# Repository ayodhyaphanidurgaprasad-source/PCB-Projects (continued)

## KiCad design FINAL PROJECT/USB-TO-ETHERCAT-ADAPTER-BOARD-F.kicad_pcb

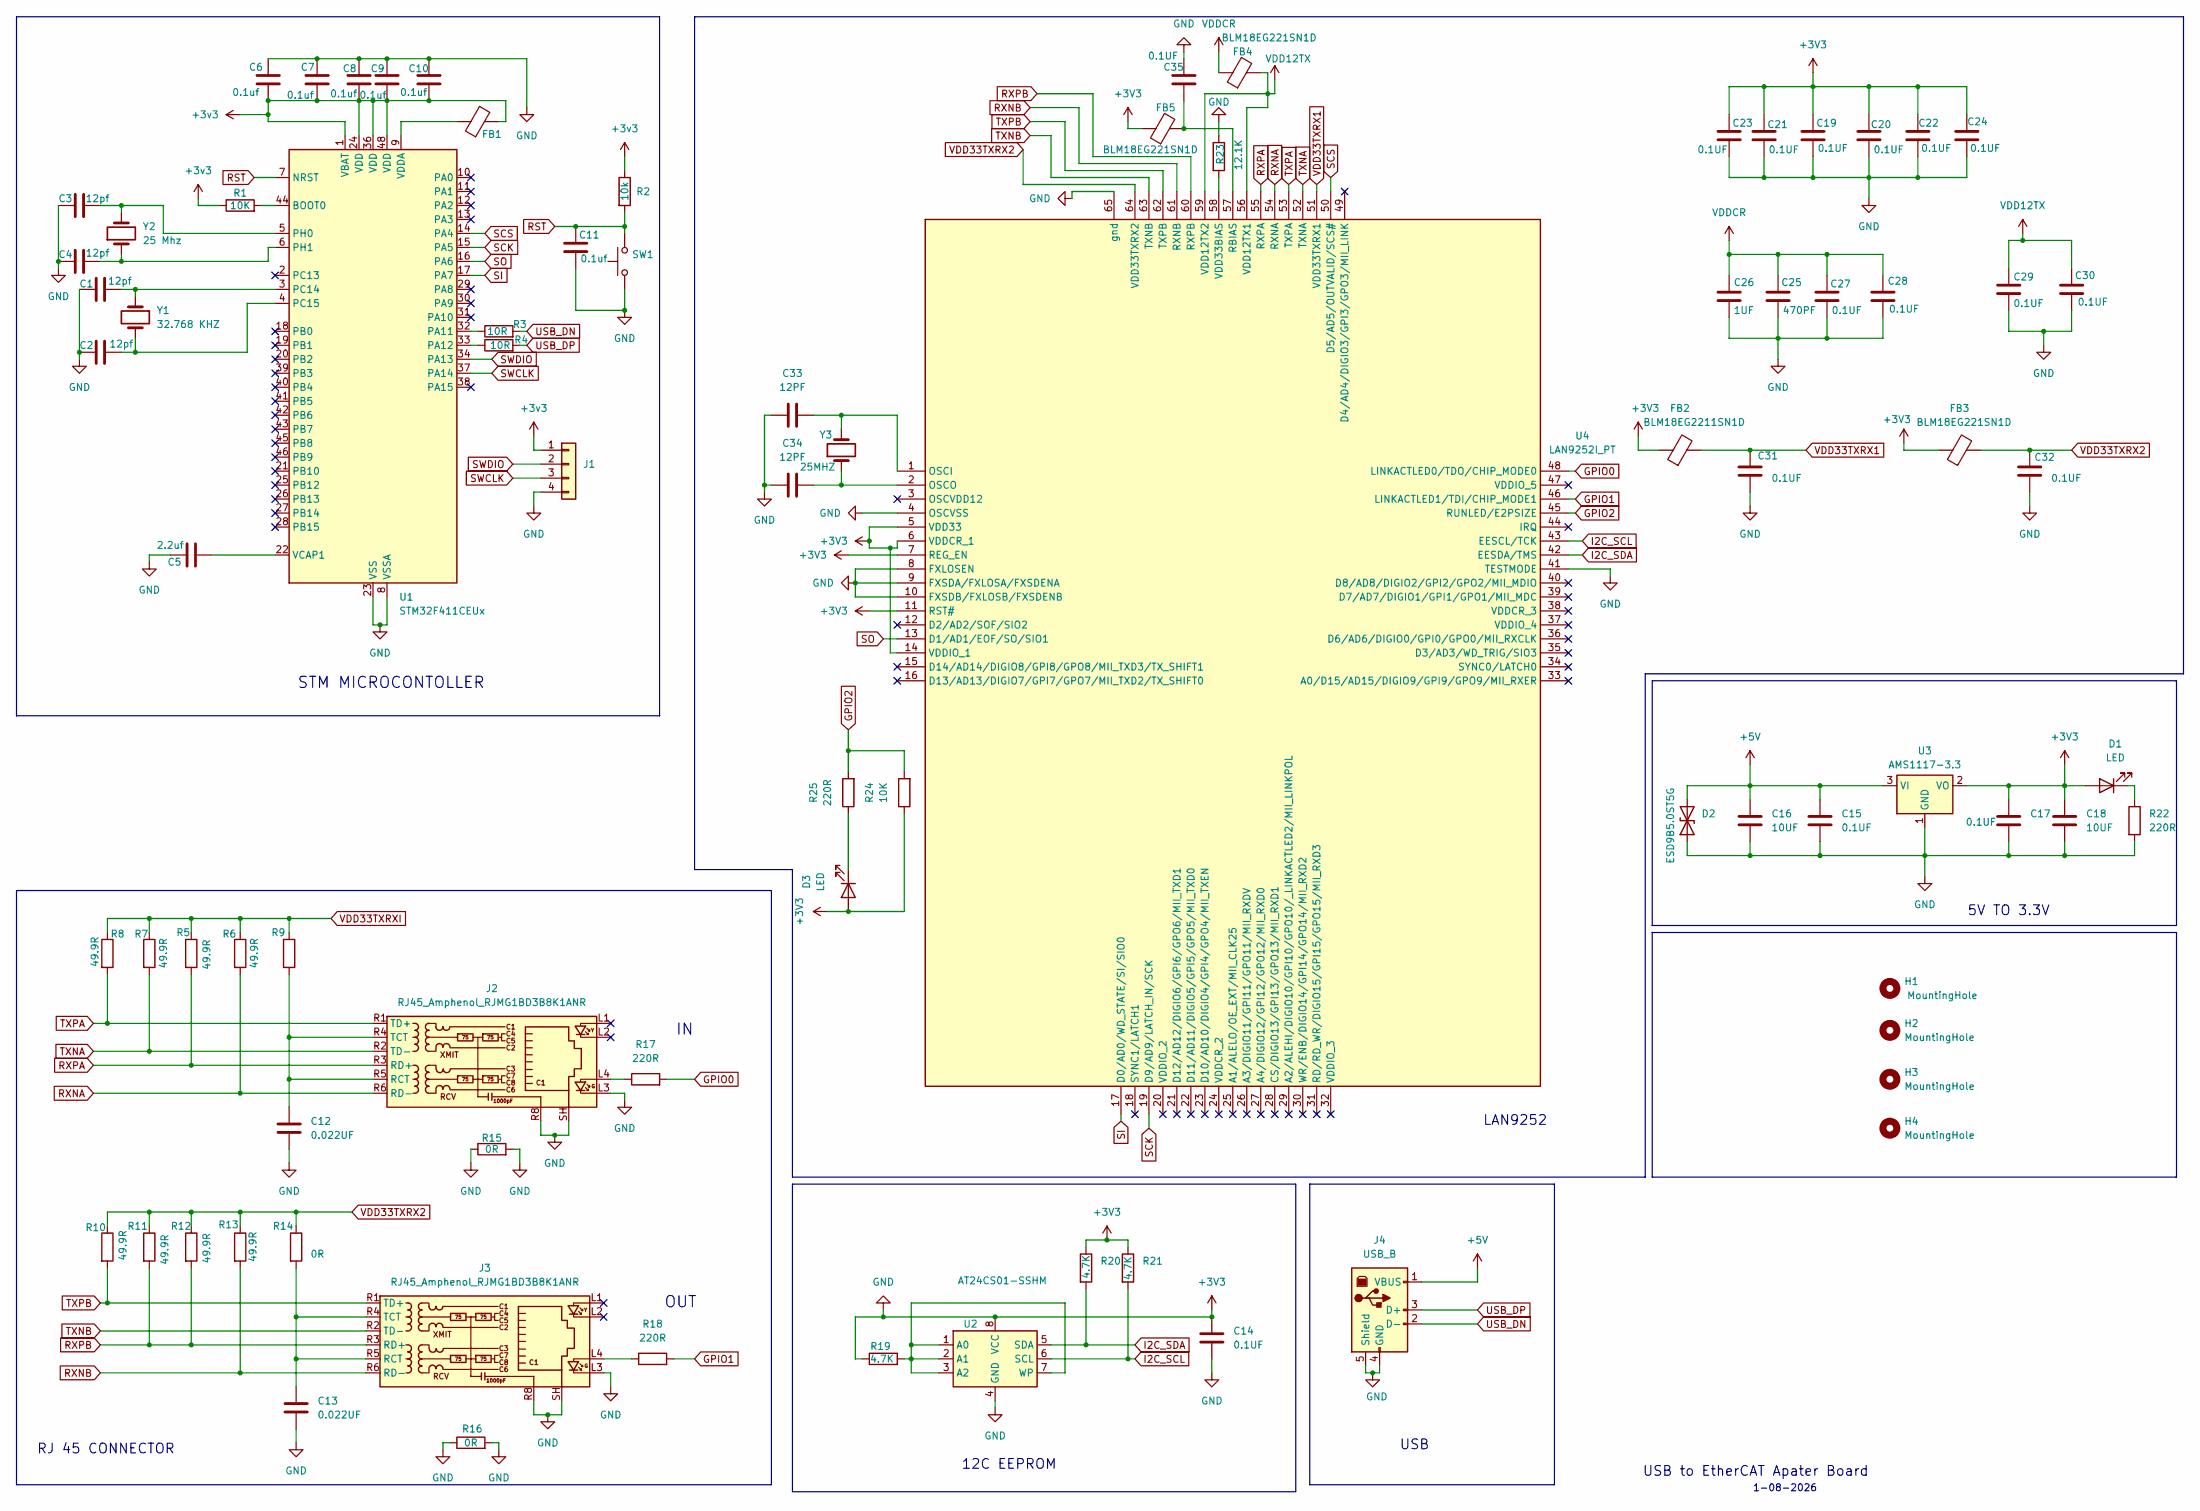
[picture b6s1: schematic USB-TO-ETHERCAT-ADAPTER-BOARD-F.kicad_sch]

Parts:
C1, C2, C3, C4: 12pf; C_0805_2012Metric
C5: 2.2uf; C_0805_2012Metric
C6, C7, C8, C9, C10, C11: 0.1uf; C_0805_2012Metric
C12, C13: 0.022UF; C_0805_2012Metric
C14, C15, C17, C19, C20, C21, C22, C23, C24, C27, C28, C29, C30, C31, C32, C35: 0.1UF; C_0805_2012Metric
C16, C18: 10UF; C_0805_2012Metric
C25: 470PF; C_0805_2012Metric
C26: 1UF; C_0805_2012Metric
C33, C34: 12PF; C_0805_2012Metric
D1, D3: LED; LED_0805_2012Metric
D2: ESD9B5.0ST5G; D_0805_2012Metric
FB1: FerriteBead; L_0603_1608Metric
FB2: BLM18EG2211SN1D; L_0603_1608Metric
FB3, FB4, FB5: BLM18EG221SN1D; L_0603_1608Metric
H1, H2, H3, H4: MountingHole; MountingHole_2.2mm_M2
J1: Conn_01x04; PinHeader_1x04_P1.27mm_Vertical
J2, J3: RJ45_Amphenol_RJMG1BD3B8K1ANR
J4: USB_B; USB_A_Molex_67643_Horizontal
R1, R24: 10K; R_0805_2012Metric
R2: 10k; R_0805_2012Metric
R3, R4: 10R; R_0805_2012Metric
R5, R6, R7, R8, R10, R11, R12, R13: 49.9R; R_0805_2012Metric
R9: R_0805_2012Metric
R14, R15, R16: 0R; R_0805_2012Metric
R17, R18, R22, R25: 220R; R_0805_2012Metric
R19, R20, R21: 4.7K; R_0805_2012Metric
R23: 12.1K; R_0805_2012Metric
SW1: SW_Push; SW_Push_SPST_NO_Alps_SKRK
U1: STM32F411CEUx; QFN-48-1EP_7x7mm_P0.5mm_EP5.15x5.15mm
U2: AT24CS01-SSHM; SOIC-8_3.9x4.9mm_P1.27mm
U3: AMS1117-3.3; SOT-223-3_TabPin2
U4: LAN9252I_PT; QFP50P1200X1200X120-65N; Manufacturer_Part_Number LAN9252I/PT; Mouser Part Number 579-LAN9252I/PT
Y1: 32.768 KHZ; Crystal_SMD_3215-2Pin_3.2x1.5mm
Y2: 25 Mhz; Crystal_SMD_HC49-SD
Y3: 25MHZ; Crystal_SMD_HC49-SD

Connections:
+5V: C15.1, C16.1, D2.2 (A2), J4.1 (VBUS), U3.3 (VI)
GPIO0: R17.2, U4.48 (LINKACTLED0/TDO/CHIP_MODE0)
GPIO1: R18.2, U4.46 (LINKACTLED1/TDI/CHIP_MODE1)
GPIO2: R24.2, R25.2, U4.45 (RUNLED/E2PSIZE)
I2C_SCL: R21.2, U2.6 (SCL), U4.43 (EESCL/TCK)
I2C_SDA: R20.2, U2.5 (SDA), U4.42 (EESDA/TMS)
unnamed: D1.1 (K), R22.1
unnamed: D3.1 (K), R25.1
unnamed: J2.L4, R17.1
unnamed: C12.1, J2.R4 (TCT), J2.R5 (RCT), R9.2
unnamed: J3.L4, R18.1
unnamed: C13.1, J3.R4 (TCT), J3.R5 (RCT), R14.2
unnamed: R1.2, U1.44 (BOOT0)
unnamed: R3.1, U1.32 (PA11)
unnamed: R4.1, U1.33 (PA12)
unnamed: C1.2, U1.3 (PC14), Y1.1
unnamed: C2.2, U1.4 (PC15), Y1.2
unnamed: C3.2, U1.5 (PH0), Y2.2
unnamed: C4.2, U1.6 (PH1), Y2.1
unnamed: C5.2, U1.22 (VCAP1)
unnamed: FB1.1, U1.9 (VDDA)
unnamed: R19.2, U2.1 (A0), U2.2 (A1), U2.3 (A2), U2.7 (WP)
unnamed: C33.2, U4.1 (OSCI), Y3.2
unnamed: C34.2, U4.2 (OSCO), Y3.1
unnamed: C35.2, FB5.2, U4.57 (RBIAS)
unnamed: R23.2, U4.58 (VDD33BIAS)
RST: C11.1, R2.2, SW1.2, U1.7 (NRST)
RXNA: J2.R6 (RD-), R6.2, U4.54 (RXNA)
RXNB: J3.R6 (RD-), R13.2, U4.61 (RXNB)
RXPA: J2.R3 (RD+), R5.2, U4.55 (RXPA)
RXPB: J3.R3 (RD+), R11.2, R12.2, U4.60 (RXPB)
SCK: U1.15 (PA5), U4.19 (D9/AD9/LATCH_IN/SCK)
SCS: U1.14 (PA4), U4.50 (D5/AD5/OUTVALID/SCS#)
SI: U1.17 (PA7), U4.17 (D0/AD0/WD_STATE/SI/SIO0)
SO: U1.16 (PA6), U4.13 (D1/AD1/EOF/SO/SIO1)
SWCLK: J1.3, U1.37 (PA14)
SWDIO: J1.2, U1.34 (PA13)
TXNA: J2.R2 (TD-), R7.2, U4.52 (TXNA)
TXNB: J3.R2 (TD-), U4.63 (TXNB)
TXPA: J2.R1 (TD+), R8.2, U4.53 (TXPA)
TXPB: J3.R1 (TD+), R10.2, U4.62 (TXPB)
USB_DN: J4.2 (D-), R3.2
USB_DP: J4.3 (D+), R4.2
VDD12TX: C29.1, C30.1, FB4.2, U4.56 (VDD12TX1), U4.59 (VDD12TX2)
VDD33TXRX1: C31.1, FB2.2, U4.51 (VDD33TXRX1)
VDD33TXRX2: C32.1, FB3.2, R10.1, R11.1, R12.1, R13.1, R14.1, U4.64 (VDD33TXRX2)
VDD33TXRXI: R5.1, R6.1, R7.1, R8.1, R9.1
VDDCR: C25.1, C26.1, C27.1, C28.1, FB4.1

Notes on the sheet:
OUT
LAN9252
12C EEPROM
STM MICROCONTOLLER
USB to EtherCAT Apater Board
RJ 45 CONNECTOR
USB
5V TO 3.3V
1-08-2026

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
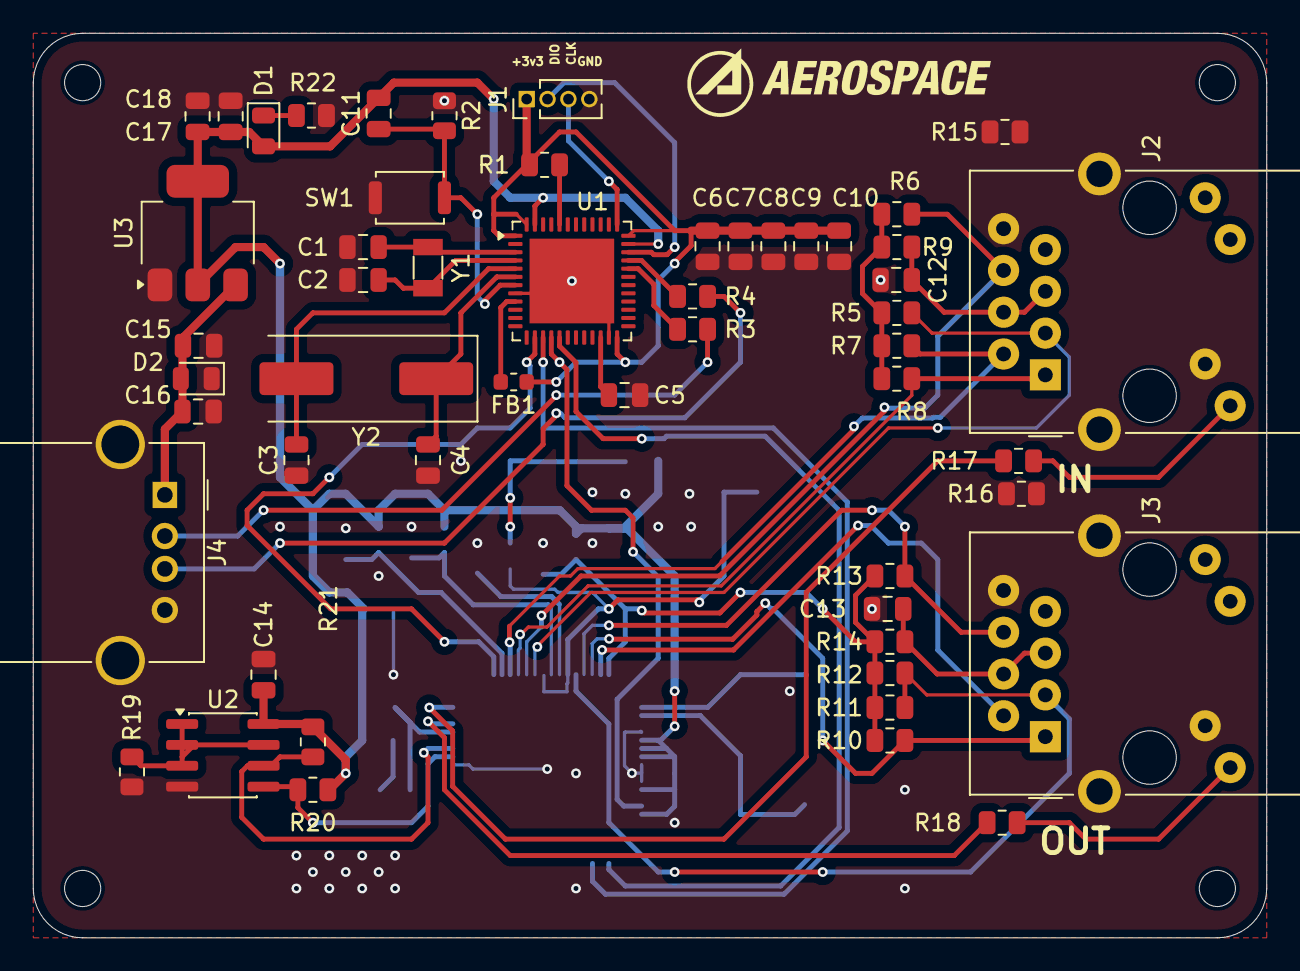
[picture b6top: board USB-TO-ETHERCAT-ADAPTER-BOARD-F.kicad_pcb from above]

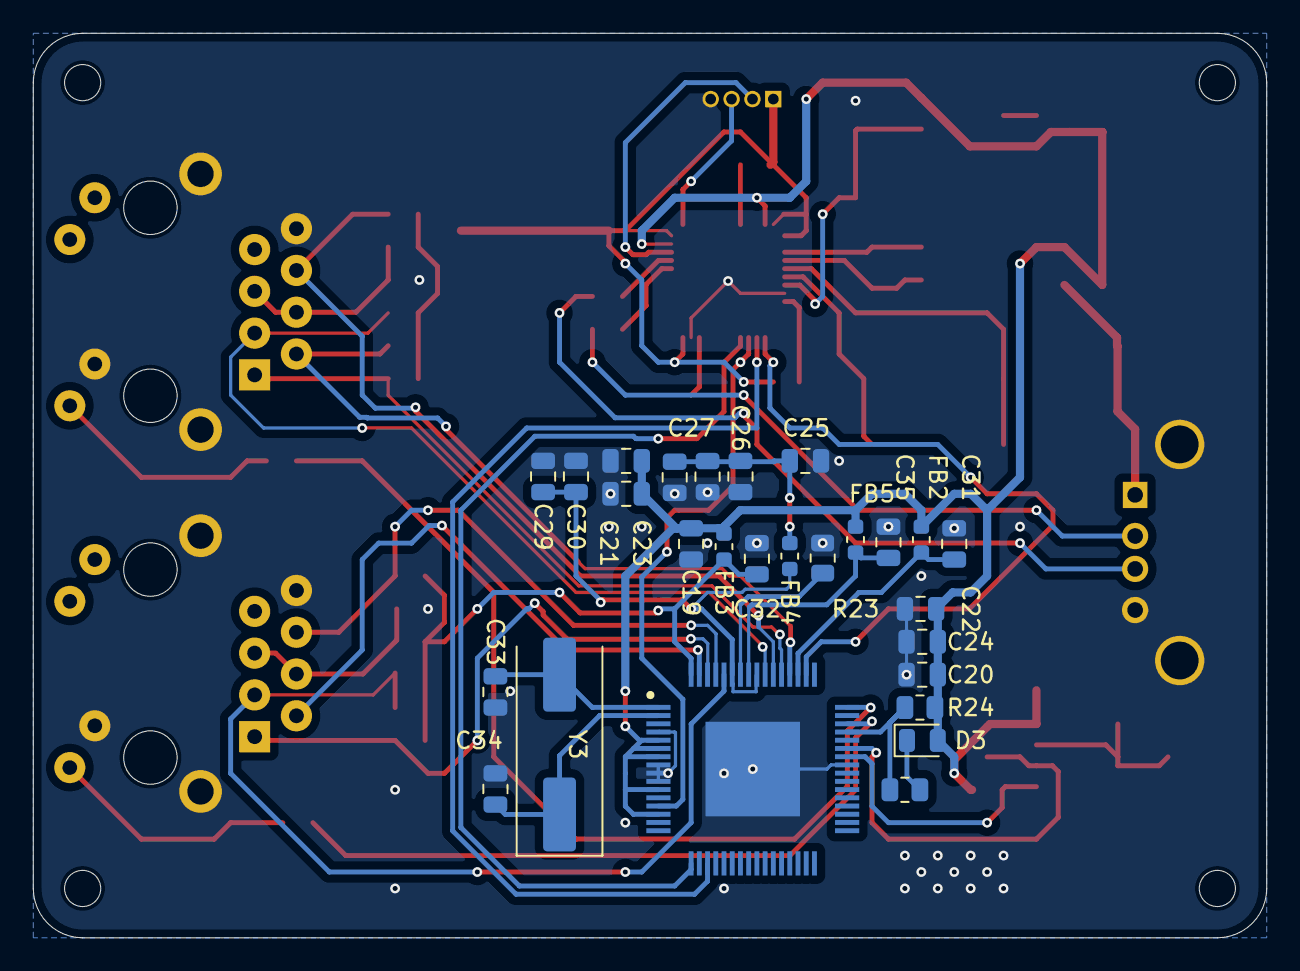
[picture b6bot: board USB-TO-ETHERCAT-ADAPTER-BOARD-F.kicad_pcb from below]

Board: 2 copper layers, 75.0 x 55.0 mm, 84 parts (27 on the bottom side), 51 nets.
